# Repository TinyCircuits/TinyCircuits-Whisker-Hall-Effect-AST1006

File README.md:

# TinyCircuits-Wireling-Hall-Effect
# AST1006 Rev2

The design files are located under design_files/ for the TinyCircuits AST1006 Rev 2 PCB. This is a Wireling board which is either populated for digital or analog magnetic readings.

The digital variant features a humble TCS40DLR hall effect switch with High/Low output and a switching point near 3.5mT (35 Gauss) and 1.4mT (14 Gauss) of Hysteresis built in.

The analog version features the Allegro A1454 linear hall effect sensor with 12-bit output and built in temperature compensation. This sensor works best with Ferrite type magnets.

Format is in Cadsoft Eagle format - Eagle version 6.2 was used for the original design.

For more infomation on this, check out the product page at TinyCircuits.com

# License:

Design by TinyCircuits.
All design files are released under the Creative Commons Attribution Share-Alike 3.0 License, see the following link for details: http://creativecommons.org/licenses/by-sa/3.0

All text above must be included in any redistribution or derived design

This project uses designs and concepts developed as part of the Arduino project and the LilyPad project.  The TinyCircuits design files themselves (schematics, PCB and libraries) are not directly derived from these works' design files and have been created new, however the concepts and basic architecture behind the TinyDuino and TinyLily products are derived and we thank the hard work of the organizations below for their contributions to open-source hardware:
  
Original Arduino Uno Design by Team Arduino

LilyPad Arduino Design by Leah Buechley and Sparkfun Electronics

Please support the open-source hardware community

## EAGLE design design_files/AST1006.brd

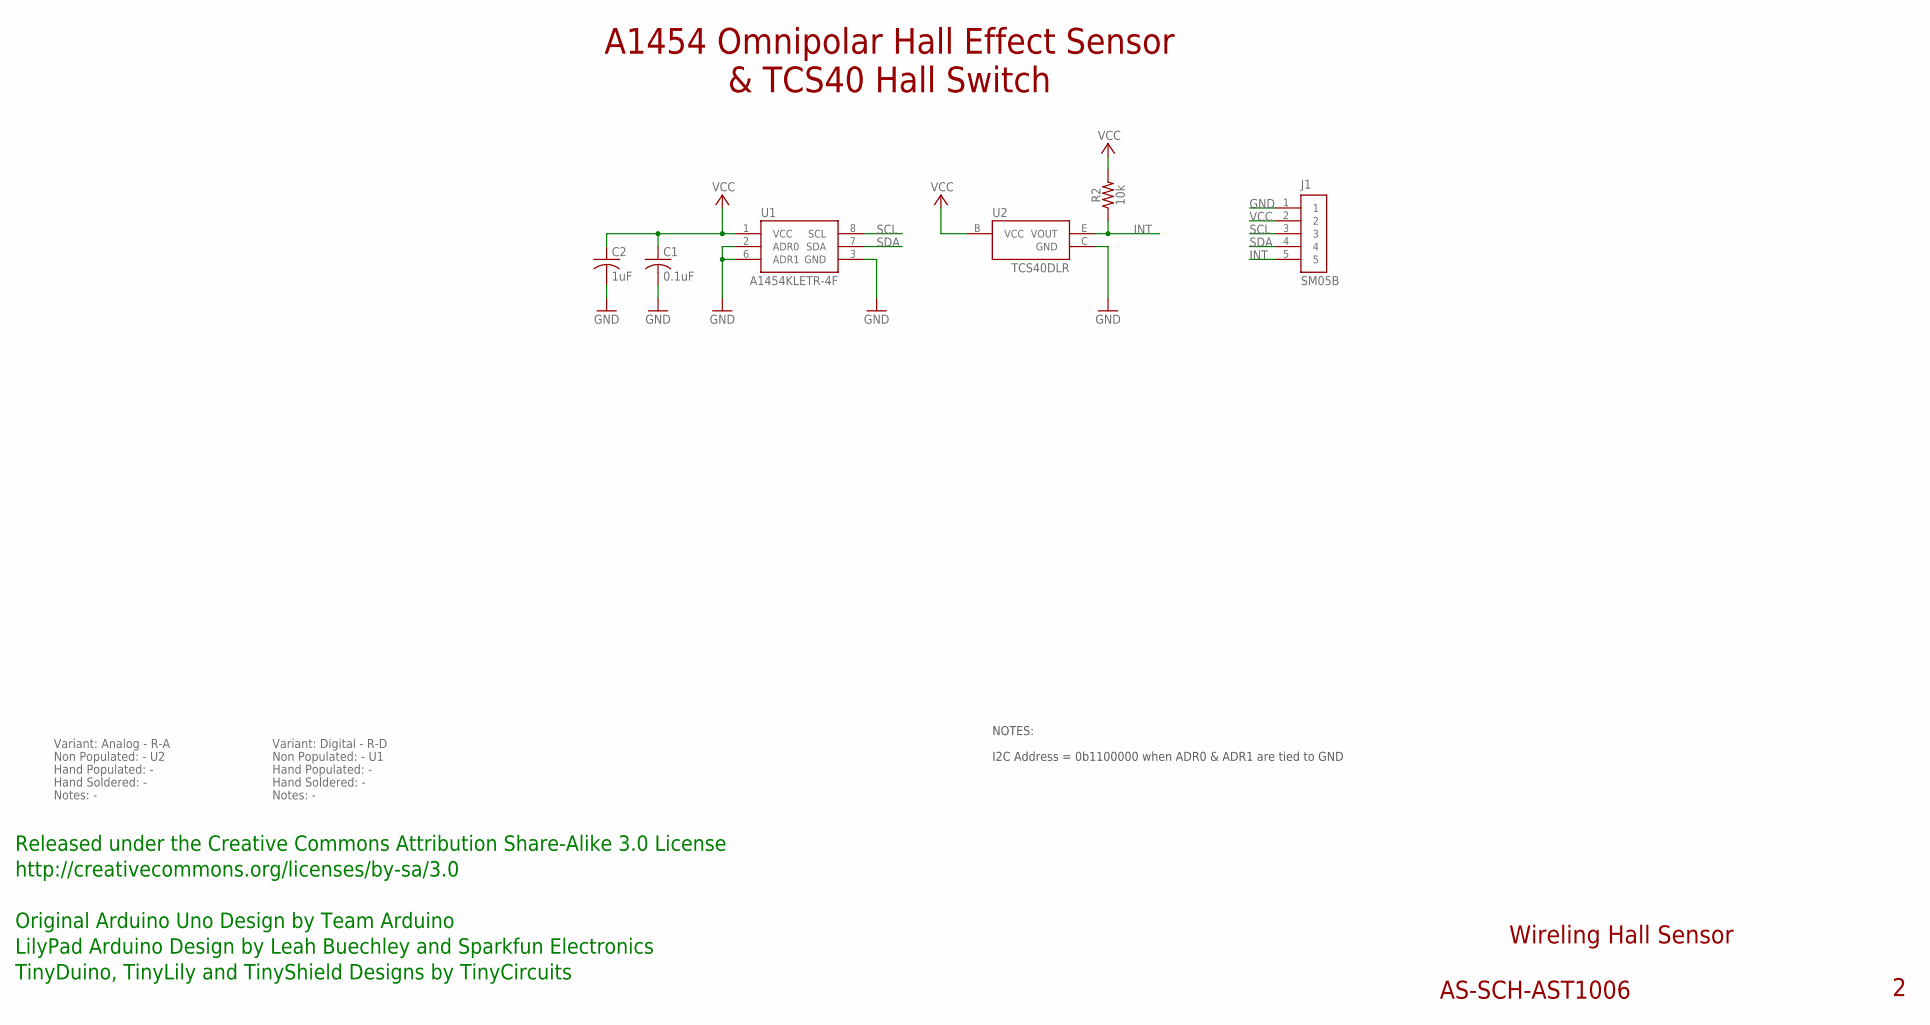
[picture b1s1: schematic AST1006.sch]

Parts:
C1: 0.1uF; C0402
C2: 1uF; C0603; PARTNO AS-ITM-00410
J1: SM05B; JST_SH_5X1_EDGE
R2: 10k; 0402; PARTNO AS-ITM-00032
U1: A1454KLETR-4F; TSSOP(8)
U2: TCS40DLR; SOT23A

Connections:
GND: C1.2, C2.2, J1.1, U1.2 (ADR0), U1.3 (GND), U1.6 (ADR1), U2.C (GND)
INT: J1.5, R2.1, U2.E (VOUT)
SCL: J1.3, U1.8 (SCL)
SDA: J1.4, U1.7 (SDA)
VCC: C1.1, C2.1, J1.2, R2.2, U1.1 (VCC), U2.B (VCC)

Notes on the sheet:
Wireling Hall Sensor
AS-SCH-AST1006
A1454 Omnipolar Hall Effect Sensor
Released under the Creative Commons Attribution Share-Alike 3.0 License
http://creativecommons.org/licenses/by-sa/3.0
Original Arduino Uno Design by Team Arduino
TinyDuino, TinyLily and TinyShield Designs by TinyCircuits
LilyPad Arduino Design by Leah Buechley and Sparkfun Electronics
NOTES:
I2C Address = 0b1100000 when ADR0 & ADR1 are tied to GND
& TCS40 Hall Switch
Non Populated: - U2
Hand Populated: -
Hand Soldered: -
Variant: Analog - R-A
Notes: -
Non Populated: - U1
Variant: Digital - R-D

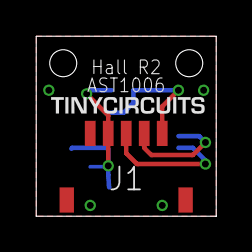
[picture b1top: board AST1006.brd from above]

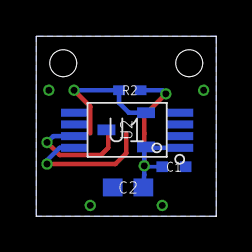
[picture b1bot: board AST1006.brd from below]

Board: 2 copper layers, 10.0 x 10.0 mm, 7 parts (5 on the bottom side), 5 nets.

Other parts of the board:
U$1: DOCFIELD-TINYCIRCUITS-PCB

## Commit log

2019-07-30 updated to use Port 0
2019-08-02 added datasheets
2019-08-12 fix program
2019-09-27 digital program
2019-09-27 pics
2019-10-28 name updates
2019-12-03 gifs
2019-12-17 updated documentation
2020-01-13 images:
2020-01-13 naming
2020-01-31 fix analog issue
2020-02-04 image
2020-02-04 I am awful at spelling I guess
2020-02-04 mass image update
2020-06-23 update hall switch code to work with TinyDuino
2020-08-14 Add CAD data
